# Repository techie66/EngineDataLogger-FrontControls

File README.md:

# Engine Data Logger - Front Controls

## Componenents
- [EngineDataLogger(EDL)](https://github.com/techie66/EngineDataLogger)
- [EDL - Dashboard](https://github.com/techie66/EngineDataLogger---Dashboard)
- ->[EDL - Front Controls](https://github.com/techie66/EngineDataLogger-FrontControls)
- [EDL - EngineData](https://github.com/techie66/EngineDataLogger-EngineData)

# Dependencies
- Seeed Studio CAN Library `git clone "https://github.com/Seeed-Studio/Seeed_Arduino_CAN.git"`

# License
EngineDataLogger is licensed under the GNU GPLv2. Dependencies are licensed under their respective licenses. See LICENSE for full text of GPLv2.

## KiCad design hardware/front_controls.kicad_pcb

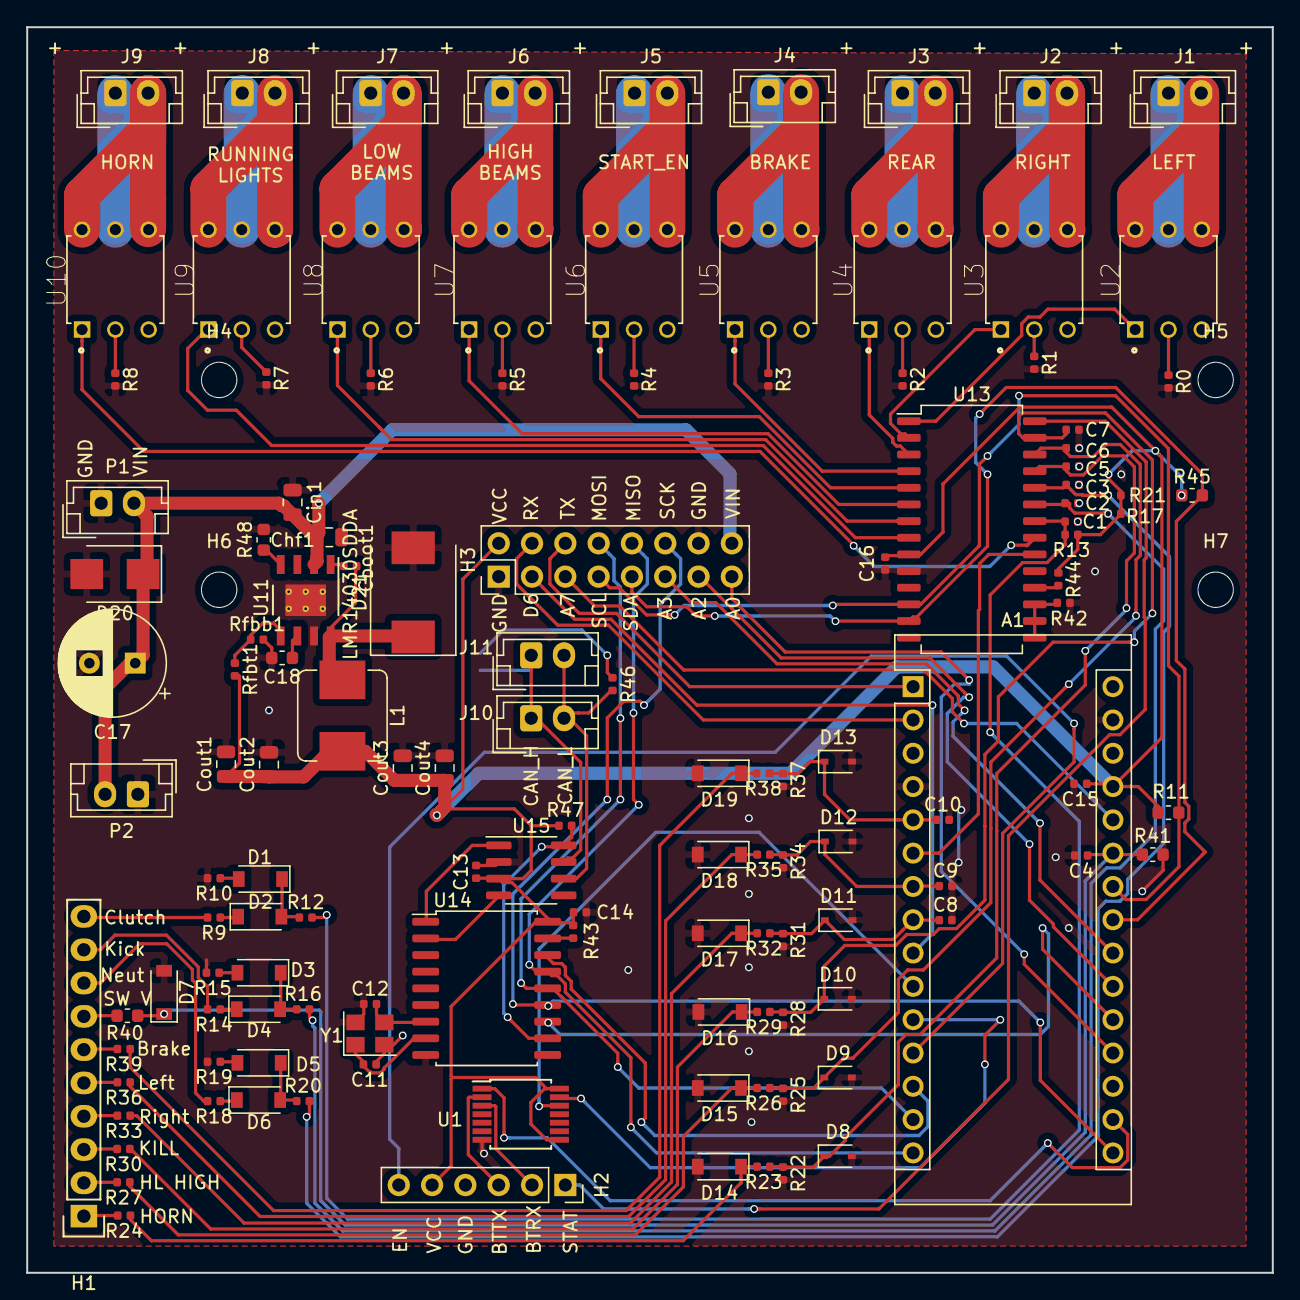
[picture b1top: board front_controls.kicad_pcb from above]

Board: 2 copper layers, 95.0 x 95.0 mm, 135 parts (1 on the bottom side), 112 nets.

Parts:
A1: Arduino_Nano_v3.x; Arduino_Nano
C1, C2, C3, C5, C6, C7, C8, C9, C10: .01uf; C_0402_1005Metric
C4: .1uf; C_0402_1005Metric
C11, C12: 33pf; C_0402_1005Metric
C13, C14, C15, C16: 100nf; C_0402_1005Metric
C17: 330uf; CP_Radial_D8.0mm_P3.50mm
C18: 22nF; C_0603_1608Metric
Cboot1: 0.1uf; C_0402_1005Metric
Chf1: 220nf; C_0805_2012Metric
Cin1: 10uf; C_0805_2012Metric
Cout1, Cout2, Cout3, Cout4: 22uF; C_0805_2012Metric
D1, D2, D3, D4, D5, D6, D14, D15, D16, D17, D18, D19: D_Schottky; D_SOD-123
D7: 5.1V Zener; D_SOD-123
D8, D9, D10, D11, D12, D13: 4.7V Zener; D_SOD-323
D20: 15V standoff; D_SMB
D21: 8A; D_SMC
H1: CONN_01X10; Pin_Header_Straight_1x10
H2: HM-10; PinSocket_1x06_P2.54mm_Vertical
H3: Expansion; PinHeader_2x08_P2.54mm_Vertical
H4, H5, H6, H7: MountingHole; MountingHole_2.7mm_M2.5
J1, J2, J3, J4, J5, J6, J7, J8, J9: Conn_01x02; JST_EH_B2B-EH-A_1x02_P2.50mm_Vertical
J10, J11: CAN; JST_EH_B2B-EH-A_1x02_P2.50mm_Vertical
JP1: Jumper_NO_Small; SolderJumper-2_P1.3mm_Open_RoundedPad1.0x1.5mm
L1: 8.2uH, 60m; L_Bourns_SRP7028A_7.3x6.6mm
P1, P2: PWR; JST_EH_B2B-EH-A_1x02_P2.50mm_Vertical
R0, R1, R2, R3, R4, R5, R6, R7, R8: 500R; R_0402_1005Metric
R9, R10, R12, R14, R15, R16, R18, R19, R20, R23, R26, R29, R32, R35, R38: 1k; R_0402_1005Metric
R11, R45: 4k7; R_0603_1608Metric
R13, R17, R21, R22, R25, R28, R31, R34, R37, R43, R44, R47: 100k; R_0402_1005Metric
R24, R27, R30, R33, R36, R39: 10R; R_0402_1005Metric
R40: 10k; R_0603_1608Metric
R41: 2k2; R_0603_1608Metric
R42: 4K7 1%; R_0402_1005Metric
R46: 120R; R_0402_1005Metric
R48: 62K11; R_0603_1608Metric
Rfbb1: 17k8 1%; R_0402_1005Metric
Rfbt1: 100k 1%; R_0402_1005Metric
U1: TXB0104PW; TSSOP-14_4.4x5mm_P0.65mm
U2, U3, U4, U5, U6, U7, U8, U9, U10: G3VM-31BR; DIP762W50P254L737H485Q6
U11: LMR14030SDDA
U13: MCP23017-E/SO; SOIC-28W_7.5x18.7mm_P1.27mm
U14: MCP2515-xSO; SOIC-18W_7.5x11.6mm_P1.27mm
U15: TJA1051T; SOIC-8_3.9x4.9mm_P1.27mm
Y1: 12Mhz; Crystal_SMD_3225-4Pin_3.2x2.5mm

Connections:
/3V3: A1.17, U1.1
/BT_EN: A1.12, H2.6
/BT_RX_H: A1.10, U1.12
/BT_RX_L: H2.2, U1.3
/BT_STATE: H2.1, U13.28
/BT_TX_H: A1.11, U1.13
/BT_TX_L: H2.3, U1.2
/CAN_H: J10.1, J11.1, JP1.1, U15.7
/CAN_INT: A1.20, U14.12
/CAN_L: J10.2, J11.2, R46.1, U15.6
/EN_TX: R47.1, U14.11, U15.8
/INTA1: A1.6, U13.20
/IN_AN1: A1.25, C4.1, D7.1, R40.2, R41.1
/IN_BRAKE: A1.5, C10.1, D13.1, R37.1, R38.1
/IN_CLUTCH: C1.1, R12.2, R13.2, U13.22
/IN_HL_HIGH: C6.1, D9.1, R25.1, R26.1, U13.26
/IN_HORN: C5.1, D8.1, R22.1, R23.1, U13.25
/IN_KICK: C2.1, R16.2, R17.2, U13.23
/IN_KILL: C7.1, D10.1, R28.1, R29.1, U13.27
/IN_LEFT: A1.7, C9.1, D12.1, R34.1, R35.1
/IN_NEUTRAL: C3.1, R20.2, R21.2, U13.24
/IN_RIGHT: A1.8, C8.1, D11.1, R31.1, R32.1
/MCU_A0: A1.19, H3.15
/MCU_A2: A1.21, H3.13
/MCU_A3: A1.22, H3.11
/MCU_A7: A1.26, H3.5
/MCU_D6: A1.9, H3.3
/OUT_BRAKE: U5.1, U13.4
/OUT_HL_HIGH: U7.1, U13.6
/OUT_HL_LOW: U8.1, U13.7
/OUT_HORN: U10.1, U13.21
/OUT_LEFT: U2.1, U13.1
/OUT_REAR: U4.1, U13.3
/OUT_RIGHT: U3.1, U13.2
/OUT_RUNNING: U9.1, U13.8
/OUT_START_EN: U6.1, U13.5
/RXCAN: U14.2, U15.4
/SCL: A1.24, H3.7, R11.1, U13.12
/SDA: A1.23, H3.9, R45.2, U13.13
/SPI_CS: A1.13, U14.16
/SPI_SCK: A1.16, H3.12, U14.13
/SPI_SI: A1.14, H3.8, U14.14
/SPI_SO: A1.15, H3.10, U14.15
/TXCAN: U14.1, U15.1
/UART_RX: A1.2, H3.4
/UART_TX: A1.1, H3.6
/VIN: C17.1, Chf1.2, Cin1.2, D20.1, H3.16, P1.2, P2.2, U11.2
GND: A1.4, A1.29, C1.2, C2.2, C3.2, C4.2, C5.2, C6.2, C7.2, C8.2, C9.2, C10.2, C11.1, C12.1, C13.2, C14.1, C15.2, C16.2, C17.2, C18.2, Chf1.1, Cin1.1, Cout1.2, Cout2.2, Cout3.2, Cout4.2, D7.2, D8.2, D9.2, D10.2, D11.2, D12.2, D13.2, D14.2, D15.2, D16.2, D17.2, D18.2, D19.2, D20.2, D21.2, H2.4, H3.1, H3.14, P1.1, P2.1, R0.2, R1.2, R2.2, R3.2, R4.2, R5.2, R6.2, R7.2, R8.2, R10.2, R15.2, R19.2, R22.2, R25.2, R28.2, R31.2, R34.2, R37.2, R41.2, R42.2, R48.2, Rfbb1.2, U1.7, U11.7, U11.9, U13.10, U14.9, U15.2, Y1.2, Y1.4
unnamed: C11.2, U14.8, Y1.1
unnamed: C12.2, U14.7, Y1.3
unnamed: C18.1, U11.6
unnamed: Cboot1.1, U11.1
unnamed: Cboot1.2, D21.1, L1.1, U11.8
unnamed: D1.1, R9.1
unnamed: D1.2, D2.1, R12.1
unnamed: D2.2, R10.1
unnamed: D3.1, R14.1
unnamed: D3.2, D4.1, R16.1
unnamed: D4.2, R15.1
unnamed: D5.1, R18.1
unnamed: D5.2, D6.1, R20.1
unnamed: D6.2, R19.1
unnamed: D14.1, R23.2, R24.1
unnamed: D15.1, R26.2, R27.1
unnamed: D16.1, R29.2, R30.1
unnamed: D17.1, R32.2, R33.1
unnamed: D18.1, R35.2, R36.1
unnamed: D19.1, R38.2, R39.1
unnamed: H1.1, R24.2
unnamed: H1.2, R27.2
unnamed: H1.3, R30.2
unnamed: H1.4, R33.2
unnamed: H1.5, R36.2
unnamed: H1.6, R39.2
unnamed: H1.7, R40.1
unnamed: H1.8, R18.2
unnamed: H1.9, R14.2
unnamed: H1.10, R9.2
unnamed: J1.1, U2.5
unnamed: J1.2, U2.6
unnamed: J2.1, U3.5
unnamed: J2.2, U3.6
unnamed: J3.1, U4.5
unnamed: J3.2, U4.6
unnamed: J4.1, U5.5
unnamed: J4.2, U5.6
unnamed: J5.1, U6.5
unnamed: J5.2, U6.6
unnamed: J6.1, U7.5
unnamed: J6.2, U7.4, U7.6
unnamed: J7.1, U8.5
unnamed: J7.2, U8.4, U8.6
unnamed: J8.1, U9.5
unnamed: J8.2, U9.6
unnamed: J9.1, U10.5
unnamed: J9.2, U10.6
unnamed: JP1.2, R46.2
unnamed: R0.1, U2.2
unnamed: R1.1, U3.2
unnamed: R2.1, U4.2
unnamed: R3.1, U5.2
unnamed: R4.1, U6.2
unnamed: R5.1, U7.2
unnamed: R6.1, U8.2
unnamed: R7.1, U9.2
unnamed: R8.1, U10.2
unnamed: R42.1, U13.15, U13.16, U13.17
unnamed: R43.1, U14.17
unnamed: R44.2, U13.18
unnamed: R48.1, U11.4
unnamed: Rfbb1.1, Rfbt1.1, U11.5
VCC: A1.27, C13.1, C14.2, C15.1, C16.1, Cout1.1, Cout2.1, Cout3.1, Cout4.1, H2.5, H3.2, L1.2, R11.2, R13.1, R17.1, R21.1, R43.2, R44.1, R45.1, R47.2, Rfbt1.2, U1.8, U1.14, U13.9, U14.18, U15.3

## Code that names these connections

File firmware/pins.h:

// PORTD
const uint8_t brakeInPin = 2;
const uint8_t leftInPin = 4;
const uint8_t rightInPin = 5;

// 3.3V pins labeled BTTX and BTRX
const uint8_t BTRX = 7;
const uint8_t BTTX = 8;

// Bluetooth "EN"
const uint8_t BT_EN = 9;

// mcp2515 interrupt
#define CAN_INT A1
const int CAN_CS_PIN = 10;

// SPI Pins
// SPI_MOSI = 11;
// SPI_MISO = 12;
// SPI_SCK = 13; // turns on LED dim when active

// MCP_GPIOA
const uint8_t hornOutPin = B00000001;
const uint8_t clutchInPin = B00000010;
const uint8_t kickInPin = B00000100;
const uint8_t neutralInPin = B00001000;
const uint8_t hornInPin = B00010000;
const uint8_t hlhighInPin = B00100000;
const uint8_t killInPin = B01000000;
const uint8_t BTStatePin = B10000000;

// MCP_GPIOB
const uint8_t leftOutPin = B00000001;
const uint8_t rightOutPin = B00000010;
const uint8_t rearOutPin = B00000100;
const uint8_t killOutPin = B00000100; // Ignition (coils, ignition module)
const uint8_t brakeOutPin = B00001000;
const uint8_t startEnableOutPin = B00010000;
const uint8_t startOutPin = B00010000; // starter
const uint8_t hlhighOutPin = B00100000;
const uint8_t hllowOutPin = B01000000;
const uint8_t runningOutPin = B10000000;

// PORTC
const uint8_t voltageInPin = A6;


/*
 * Constants for Cmd flags
const uint8_t ENGINE_RUNNING = B10000000;       // serialCmdA
const uint8_t BRAKE_ON = B00000100;             //receivedCmdD
const uint8_t HORN_ON = B00001000;              //receivedCmdD
const uint8_t LEFT_ON = B00010000;              //receivedCmdD
const uint8_t RIGHT_ON = B00100000;             //receivedCmdD
const uint8_t HIGH_BEAMS_ON = B01000000;        //receivedCmdD
const uint8_t KILL_ON = B10000000;              //receivedCmdD

const uint8_t CLUTCH_DISENGAGED = B00000100;    //receivedCmdC
const uint8_t IN_NEUTRAL  = B00010000;          //receivedCmdC
const uint8_t KICKSTAND_UP = B00001000;         //receivedCmdC
 */

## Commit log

2019-03-16 Initial commit with fairly well tested code. Had been developed previously with Arduino library before switching to Make and git.
2019-04-22 Create LICENSE
2020-09-08 Folder structure. PCB KiCAD files.
2020-09-10 License Update
2021-04-18 Version 2 hardware files
2021-05-15 Initial software rewrite for V2 hardware
2021-05-15 Hardware V2 major modifications
2021-05-15 Makefile options to work better with older tool-chains
2021-07-06 use new hardware power saving features
2021-07-09 Corrected low-power states for TJA1051T
2021-08-26 Switched regulators to more available chip
2021-09-14 typo cleanup
2021-09-14 Disable code that uses repurposed pins
2021-09-15 Logic added for kill-switch output
2021-09-15 Added state var for powerOn
2021-09-15 Changed aux board to usable pin
2021-09-16 Basic power control via BLE module INSECURE, no auth or anything. ANY connection turns on the power. Some work with keeping the MLT-BT05 I have responsive and sleeping.
2021-09-17 Updated Killswitch/Kickstand Logic. Add power-off protection for BLE disconnects.
2022-08-01 gps, imu additional modules. WDT, CANSerial support. include spinner and pins defined in different header
2022-09-11 combined gps and imu to one device
2022-09-12 #defines for BLE power control, listens to CAN for incoming commands
2022-09-12 updated dependancy in readme
2022-09-12 disable WDT on sleep, read CAN bus properly
2022-09-25 gps+imu: Disable WDT during setup, change MPU6050 address
2022-09-26 shrunk program size. fixed watchdog
2022-10-26 save space on gps+imu, sleep, and power management. Split out some more common functions
2022-10-30 fixed to match actual hardware
2023-04-19 Assume engine running if voltage > 14. Helps keep headlight on if CAN fails
2023-04-19 fixed typo
2023-04-25 handle watchdog better on main program like we started doing with the extra sketches
2023-04-26 prevent race condition with BLE module, move a few pin definitions to pins.h
2023-07-30 Changed out BLE module, no communication needed. Different wake detection.
2023-08-03 Refactor main frontcontrols to use functions.h. Add testing for auto blinker cancel
2023-08-03 Removed workaround for CAN library
2023-08-03 Need to run Wakeup_Routine after waking up...
2023-08-03 Create inputCmd from toggle bits to maintain interop with external API
2023-08-03 Update auto cancel logic
2023-08-04 Added missing interrupt vector, inserted delay in sleep routine.
2023-08-04 Auto Canceling blinkers working
2023-08-05 Add OBD response support
2024-02-29 Update Kicad files
2024-03-02 Add emulation of OBDLink Adapter
2024-04-12 Rate limit gps+imu. Rate limit BT.
2025-08-16 Removed space from serial output of CAN data

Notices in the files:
parts and their libraries:
Copyright 2016 Accelerated Designs. All rights reserved.
